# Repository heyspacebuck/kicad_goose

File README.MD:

# Horrible Goose Badge SAO

[@Gnarflordius](https://twitter.com/Gnarflordius) made a KiCad footprint of the Horrible Goose so I turned it into a set of capacitive-touch boards that function as [Simple Add-Ons](https://hackaday.com/2019/03/20/introducing-the-shitty-add-on-v1-69bis-standard/). All the boards are based on the [Atmel AT42QT101x chips](http://ww1.microchip.com/downloads/en/DeviceDoc/40001947A.pdf), which are out of stock everywhere right now. Sorry. If anyone has suggestions for alternate cap-touch sensors, or knows how to set up QTouch on an ATtiny, please drop me a line.

The `/kicad` folder is set up to contain multiple projects that each rely on `goose.lib` and `\goose.pretty` for schematic symbols and PCB footprints. These projects are:

### SAO 1: Horrible Goose Cap Touch Sensor

Here we see the basic SAO. You can find it in the `/kicad` folder under the name `SAO-captouch-sensor-only.pro`. The SCL and SDA lines are not needed; the HONK pin (GPIO1, by SAO naming conventions) connects to the sensor output; the SYNC pin (GPIO2) is by default tied to ground. When the goose is touched, the HONK pin is driven HIGH; otherwise, it is pulled LOW by an internal pull-down resistor. If for whatever reason you want to mess with the default SYNC settings, you can cut the jumper that ties it to ground and instead drive it via GPIO2.

You can see this circuit (with a non-SAO pinout) connected to an Arduino in [this tweet from back in May](https://twitter.com/heyspacebuck/status/1396235318634840066). The Arduino code being used is available in the `/code/arduino_honk` folder.

### SAO 2: Horrible Goose Cap Touch Sensor - After Dark

This project is in the `kicad/` folder named `SAO-captouch-sensor-only-after-dark.pro`. It's the same circuit as above, but the "HONK" text and sensor footprint have been optimized for OSH Park's After Dark boards. 

### SAO 3: Horrible Goose, But Extra Evil

This project is in the `kicad/` folder named `SAO-captouch-and-eye-after-dark.pro`. Another After Dark board. Similar to the others, but instead of breaking out the SYNC pin, GPIO2 is used to drive a reverse-mounted LED. This makes the goose eye glow and lays bare the true nature of this horrible fowl menacing the village. [You can see it in action (kinda) here](https://twitter.com/heyspacebuck/status/1437613800312610819). KiCad thinks none of the traces are valid because I used graphic arcs instead of normal routing.

### SAO 4: Self-Contained Honking Goose Unit

This project is in the `kicad/` folder named `SAO-speaker-and-controller.pro`. Once I learned about the existence of extra-small "sugar cube" speakers, I knew I'd have to build an SAO that could function as a standalone honking device. In addition to the cap-touch IC, there's an ATtiny85 driving a 16mm×9mm speaker. Once I got the tiny speaker, it became clear that 3.3V is not sufficient to get an audible honk! I have added a simple boost converter to drive the ATtiny85 and the speaker with 5V instead of 3.3V.

The ATtiny85 is programmed with a [SOICbite connector](https://hackaday.io/project/165917-soicbite-programmingdebug-connector-footprint); if you don't have one it is easy to solder wires to the SOICbite pads. The code is in the `code/tiny85_speaker_control` folder. It's set up for compiling/programming using the Arduino IDE and ATtinyCore approach. You could also use Atmel's QT creator, since the code uses no Arduino-specific methods; just rename `tiny85_speaker_control.ino` to `main.c`.

## Licenses and acknowledgments 

The horrible goose comes from [Untitled Goose Game by House House](https://goose.game/). It's a charming game and you should check it out! The original KiCad goose footprint was designed by [@Gnarflordius](https://twitter.com/Gnarflordius) and released under a [WTFPL license](http://www.wtfpl.net/). I made some minor changes to the footprint and also created a pair of matching schematic symbols. The SAO PCBs and various bits of code are released under the [CERN Open Hardware Licence 1.2](https://en.wikipedia.org/wiki/CERN_Open_Hardware_Licence), but to be honest I'm not sure I'm using it correctly. Do what you want.

The Arduino and ATtiny85 code is derived from two sources: ["Audio Sample Player v2" by David Johnson-Davies](http://www.technoblogy.com/show?QBB) (used under CC-BY-4.0 license), and ["speaker_pcm" by Michael Smith <michael@hurts.ca>](https://playground.arduino.cc/Code/PCMAudio/) (unclear license).

The [SOICbite connector](https://hackaday.io/project/165917-soicbite-programmingdebug-connector-footprint) is an awesome little design from Simon Merrett and is released under the BSD 2-Clause "Simplified" License.

The HONK text was generated using the very cool [KiBuzzard plugin by Greg Davill](https://github.com/gregdavill/KiBuzzard).

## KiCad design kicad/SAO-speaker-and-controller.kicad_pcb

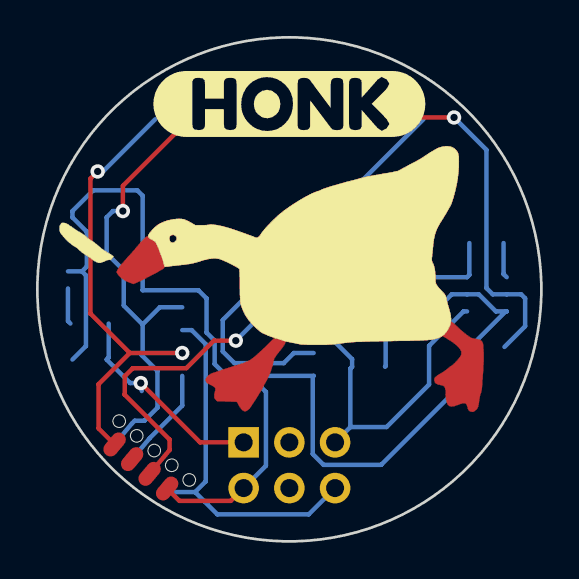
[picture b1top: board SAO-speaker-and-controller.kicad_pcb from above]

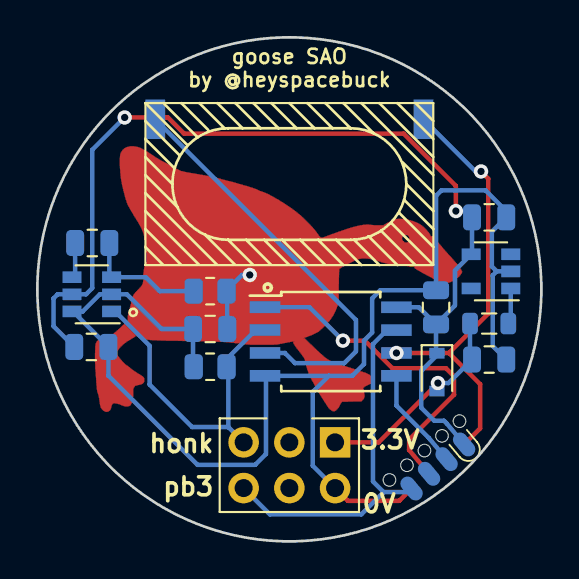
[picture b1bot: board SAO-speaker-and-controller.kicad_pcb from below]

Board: 2 copper layers, 28.0 x 28.0 mm, 18 parts (16 on the bottom side), 13 nets.

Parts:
C1, C4: 0.1 μF; C_0805_2012Metric
C2: 0.01 μF; C_0805_2012Metric
C3: 10 pF; C_0805_2012Metric
C5: 4.7 μF; C_0805_2012Metric
C6: 22 μF; C_0805_2012Metric
D1: D; D_SOD-323
GOOSE1: LOGO; honk_captouch_scaled_v2
J1: SAO Connector; PinHeader_2x03_P2.54mm_Vertical
J2: SOICbite; SOIC_clipProgSmall
L1: 2.2 μH; L_0805_2012Metric
LS1: SP-1609S 8Ω 0.5W speaker; Speaker_SP-1609S
R1, R2: 1 kΩ; R_0805_2012Metric
U1: AT42QT1011-TSHR; SOT-23-6
U2: ATtiny85-20SU; SOIJ-8_5.3x5.3mm_P1.27mm
U3: TPS613222ADBV; SOT-23-5
svg2mod: G***; label

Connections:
0V: C1.2, C3.2, C4.2, C5.2, C6.2, J1.2, J2.5, R2.1, U1.2, U1.6, U2.4, U3.2
5V: C1.1, C4.1, C6.1, D1.1, J2.1, U1.5, U2.8, U3.4
/sdi: J2.2, U2.5
/sdo: J2.8, LS1.2, U2.6
/~cs: J2.6, U2.1
unnamed: C2.1, R1.1, U1.3
unnamed: C2.2, U1.4
unnamed: C3.1, R1.2
unnamed: L1.2, U3.1
unnamed: LS1.1, U2.3
Vin: C5.1, D1.2, J1.1, L1.1
clk: J1.6, J2.4, U2.7
honk: J1.5, R2.2, U1.1, U2.2

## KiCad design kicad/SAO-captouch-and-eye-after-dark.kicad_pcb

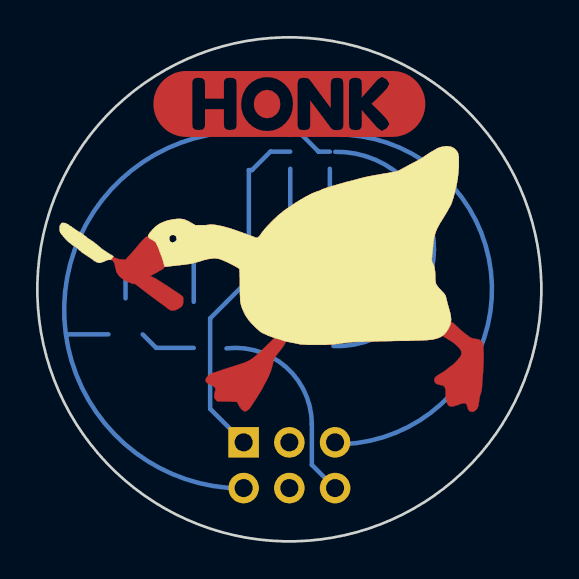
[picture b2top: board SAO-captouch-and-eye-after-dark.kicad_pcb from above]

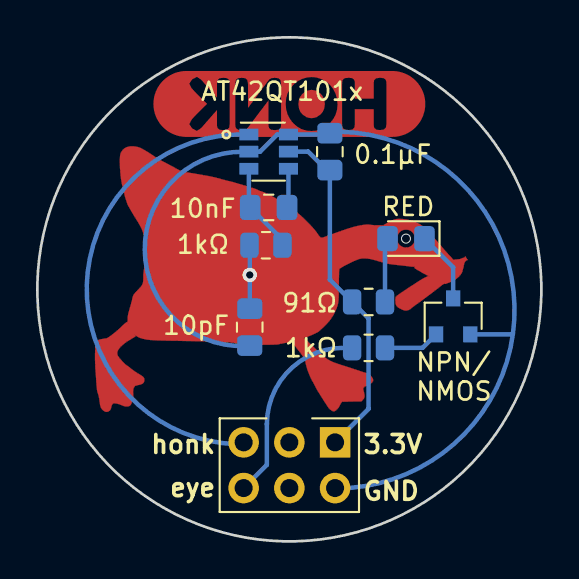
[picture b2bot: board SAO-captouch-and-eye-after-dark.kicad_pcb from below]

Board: 2 copper layers, 28.0 x 28.0 mm, 12 parts (10 on the bottom side), 10 nets.

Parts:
C1: 0.1 μF; C_0805_2012Metric_Pad1.15x1.40mm_HandSolder
C2: 0.01 μF; C_0805_2012Metric_Pad1.15x1.40mm_HandSolder
C3: 10 pF; C_0805_2012Metric_Pad1.15x1.40mm_HandSolder
D1: Reverse-mounted red 0805; LED_0805_2012Metric_Pad1.15x1.40mm_HandSolder
GOOSE1: LOGO; honk_captouch_scaled_afterdark
J1: SAO Connector; PinHeader_2x03_P2.54mm_Vertical
Q1: Q_NMOS_GSD; SOT-23
R1: 1 kΩ; R_0805_2012Metric
R2: 91Ω; R_0805_2012Metric
R3: 1kΩ; R_0805_2012Metric
U1: AT42QT1011-TSHR; SOT-23-6
svg2mod: G***; label

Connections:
0V: C1.2, C3.2, J1.2, Q1.2, U1.2, U1.6
unnamed: C2.1, R1.1, U1.3
unnamed: C2.2, U1.4
unnamed: C3.1, R1.2
unnamed: D1.1, Q1.3
unnamed: D1.2, R2.1
unnamed: Q1.1, R3.1
Vin: C1.1, J1.1, R2.2, U1.5
eye: J1.6, R3.2
honk: J1.5, U1.1

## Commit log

2021-05-09 Init commit
2021-05-09 Add 3d views
2021-05-09 Added a version that uses a chip that's actually in stock
2021-05-09 Fixed jumper soldermask
2021-05-10 added resistor-stealing goose schematic symbol
2021-05-22 Added Arduino sketch
2021-05-22 Update readme and goose_R library symbol
2021-08-23 Changed to SAO connector
2021-08-23 Aaaagh
2021-08-23 Goose After Dark
2021-08-23 Soldermask on eye
2021-10-15 Dramatic restructuring
2021-11-28 Update design 4
